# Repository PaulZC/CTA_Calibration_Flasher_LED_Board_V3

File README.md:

# CTA Calibration Flasher: LED Board V3

A nanosecond LED flasher board which provides digital control of both pulse width and LED current. Designed to aid
photomultiplier detector calibration and characterisation.

The design of this board is based extensively on that of the [Nanosecond LED Flasher Shield](https://github.com/PaulZC/Nanosecond_LED_Flasher_Shield).

The LED is driven by the [LMG1025 from Texas Instruments](http://www.ti.com/product/LMG1025-Q1).
Designed for automotive LIDAR applications, this gate driver has typical rise and fall times of 650ps
and 850ps and can produce 5V pulse widths as short as 1.25ns.

The pulse width is controlled by a [Maxim Integrated DS1023S-25+](https://www.maximintegrated.com/en/products/analog/clock-generation-distribution/DS1023.html)
programmable timing element which can produce digitally-adjustable pulse widths of 0 to ~64ns in 0.25ns increments.

The LED current is set by five surface mount resistors connected in series, four of which can be shorted
out by [Toshiba TLP3475 photorelays](https://toshiba.semicon-storage.com/ap-en/semiconductor/product/optoelectronics/photorelay-mosfet-output/detail.TLP3475.html)
allowing the LED current to be adjusted digitally in 16 increments.

The board is designed to be mounted on and controlled by the [CTA Calibration Flasher Controller Board V3](https://github.com/PaulZC/CTA_Calibration_Flasher_Controller_Board_V3).

The temperature can be measured via an [ADT7310 16-bit SPI temperature sensor](https://www.analog.com/en/products/adt7310.html).

The board is also equipped with a [DS28CM00 I<sup>2</sup>C silicon serial number](https://www.maximintegrated.com/en/products/ibutton-one-wire/memory-products/DS28CM00.html)
to allow the board to be uniquely identified during calibration.

To aid the mounting of a diffuser or fibre-coupling optics, a modified [ThorLabs S1LEDM SM1 threaded mount](https://www.thorlabs.de/thorproduct.cfm?partnumber=S1LEDM)
can be mounted onto the circuit board.

Please note that this board requires 5V power but that all I/O signals are 3.3V.

## Repository Contents

- **/Documentation** - Documentation for the hardware
- **/Hardware** - BOM, schematic, Eagle PCB design files and Gerber files
- **LICENSE.md** contains the licence information

## Documentation

- [Hardware overview](./Documentation/README.md): an overview of the hardware

Enjoy!

**_Paul_**

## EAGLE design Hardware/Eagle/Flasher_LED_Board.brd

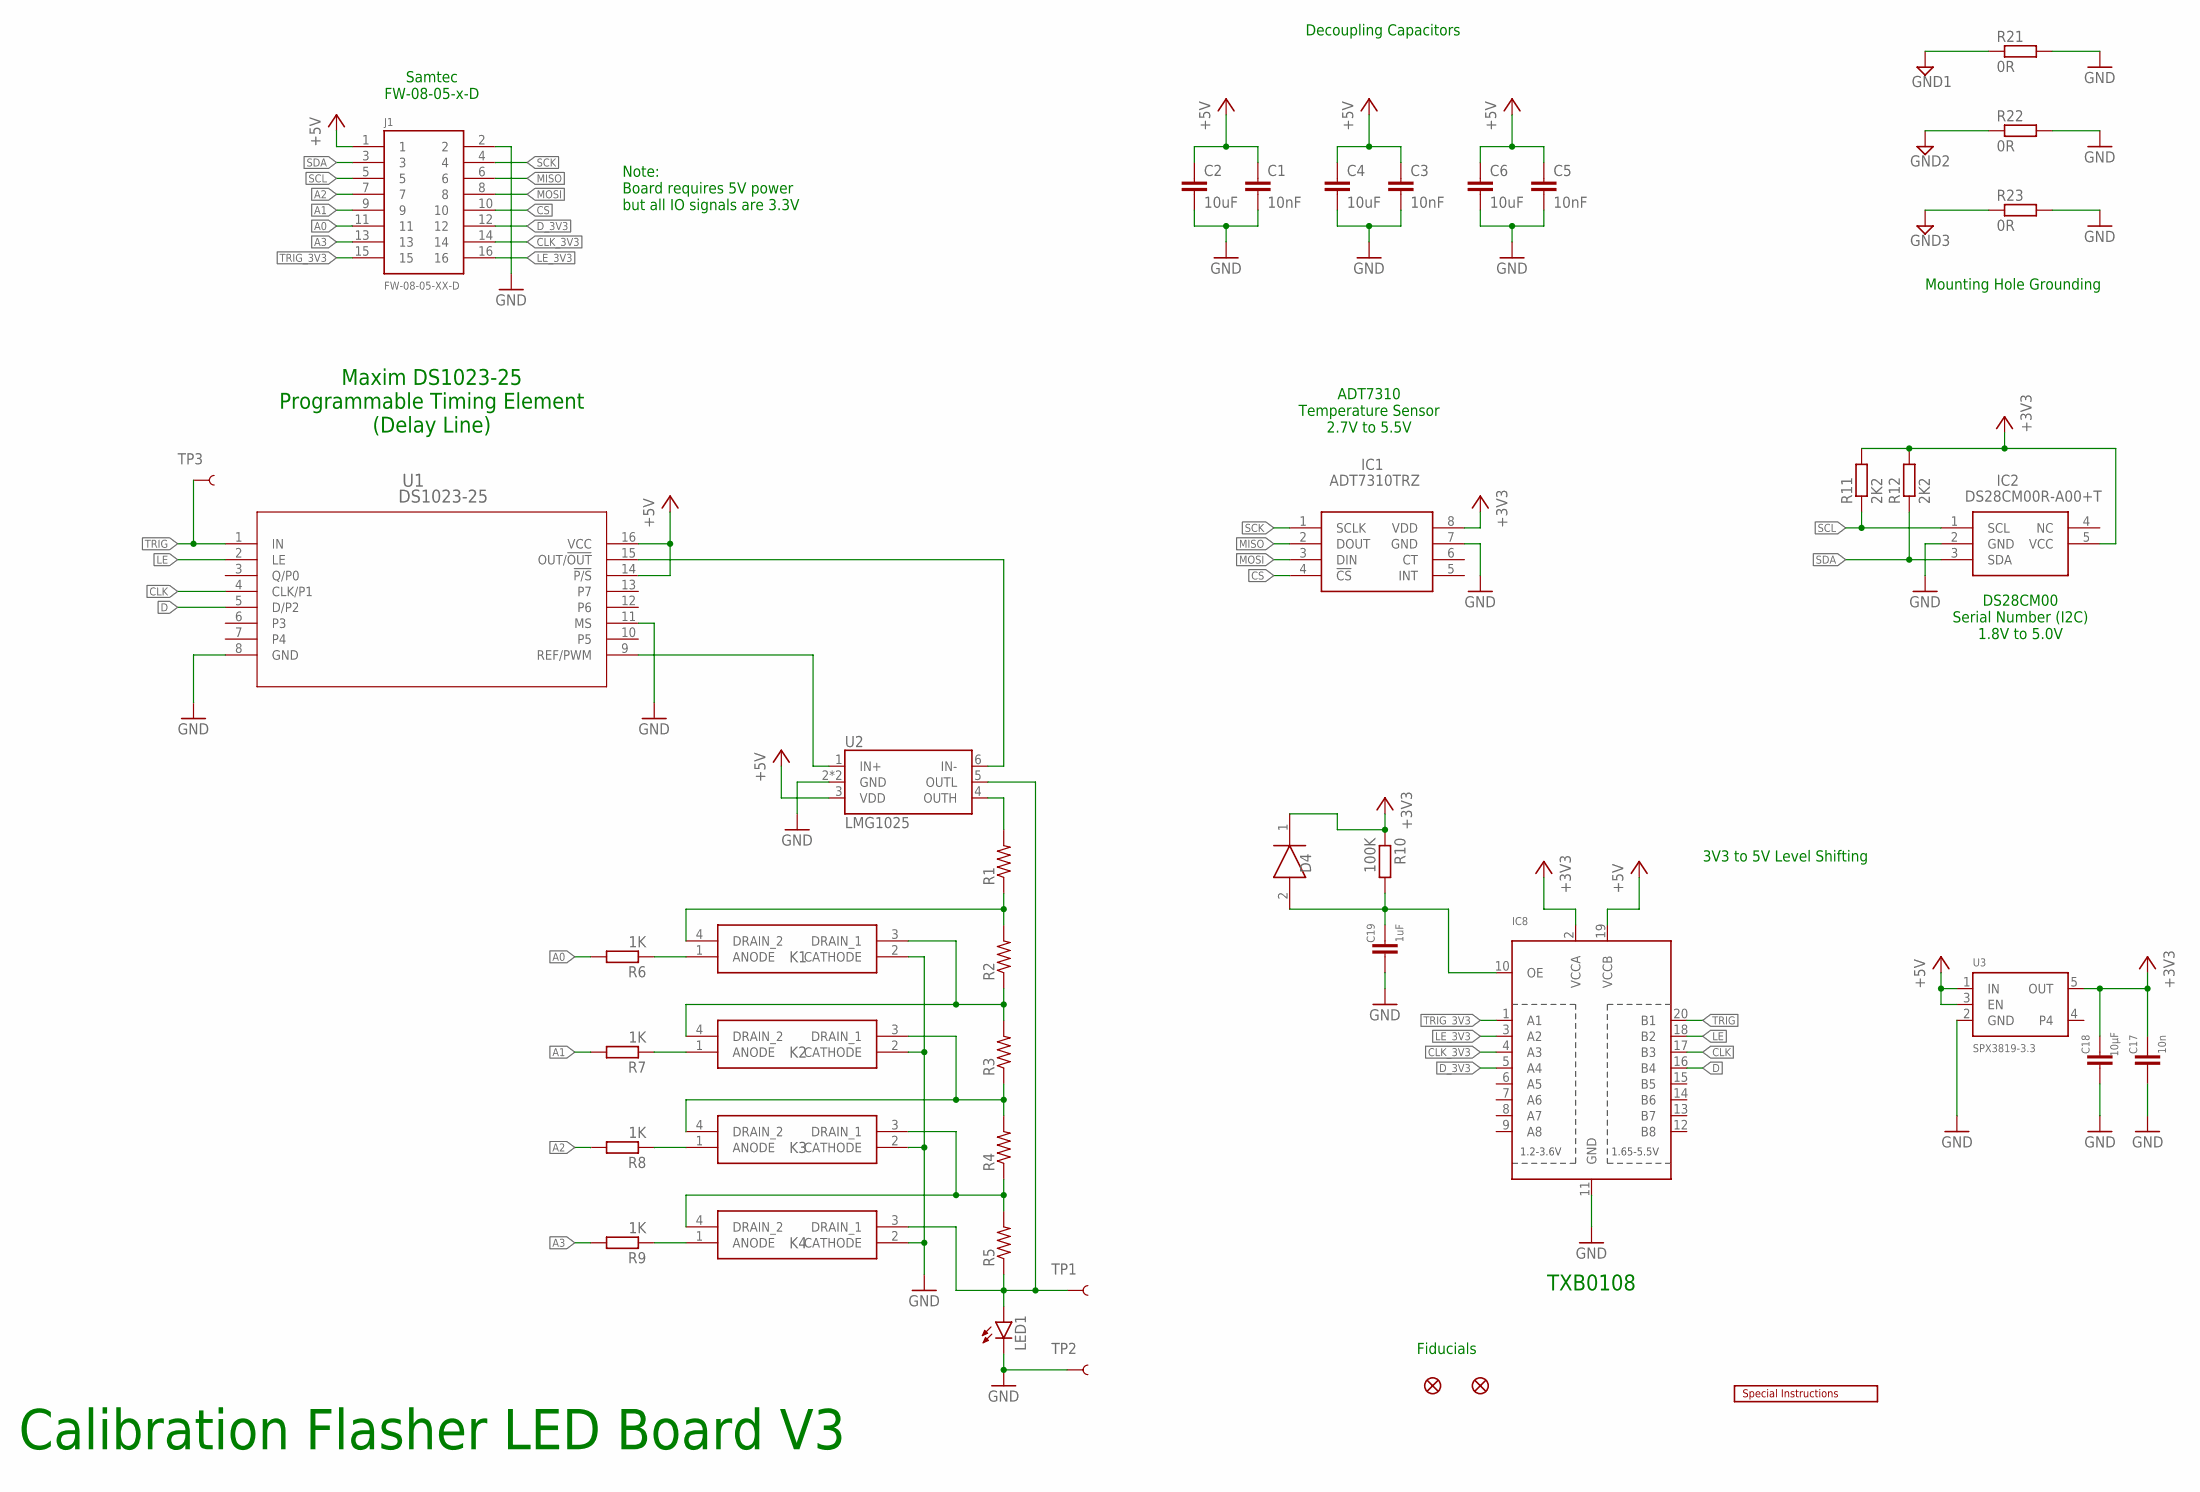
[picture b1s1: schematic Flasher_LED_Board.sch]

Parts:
C1, C3, C5: 10nF; C0805
C2, C4, C6: 10uF; C0805
C17: 10n; C0603
C18: 10µF; C0805
C19: 1uF; C0603
D4: CD0603-B00340; DIOM179X85N
FD1, FD2: FIDUCIAL1X2; FIDUCIAL-1X2
IC1: ADT7310TRZ; SOIC127P600X175-8N
IC2: DS28CM00R-A00+T; SOT95P280X145-5N
IC8: TXB0108PWR; TSSOP20
J1: FW-08-05-XX-D
K1, K2, K3, K4: TLP3475R(TP,F; TLP3475RTPF
LED1: LED3MM
LOGO6: SPECIAL_INSTRUCTIONS-ORDERING; ORDERING_INSTRUCTIONS
R1, R2, R3, R4, R5: RESISTOR0805-RES; 0805
R6, R7, R8, R9: 1K; R0603
R10: 100K; R0603
R11, R12: 2K2; R0603
R21, R22, R23: 0R; R0603
TP1, TP2, TP3: TEST-POINTPOGO_PTH; 1X01_NO_SILK
U1: DS1023-25; 21-0042B_16
U2: LMG1025
U3: SPX3819-3.3; SOT23-5

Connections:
+3V3: C17.1, C18.1, D4.1 (K), IC1.8 (VDD), IC2.5 (VCC), IC8.2 (VCCA), R10.1, R11.2, R12.2, U3.5 (OUT)
+5V: C1.1, C2.1, C3.1, C4.1, C5.1, C6.1, IC8.19 (VCCB), J1.1, U1.14 (!P/S), U1.16 (VCC), U2.3 (VDD), U3.1 (IN), U3.3 (EN)
A0: J1.11, R6.2
A1: J1.9, R7.2
A2: J1.7, R8.2
A3: J1.13, R9.2
CLK: IC8.17 (B3), U1.4 (CLK/P1)
CLK_3V3: IC8.4 (A3), J1.14
CS: IC1.4 (!CS), J1.10
D: IC8.16 (B4), U1.5 (D/P2)
D_3V3: IC8.5 (A4), J1.12
GND: C1.2, C2.2, C3.2, C4.2, C5.2, C6.2, C17.2, C18.2, C19.2, IC1.7 (GND), IC2.2 (GND), IC8.11 (GND), J1.2, K1.2 (CATHODE), K2.2 (CATHODE), K3.2 (CATHODE), K4.2 (CATHODE), LED1.K (C), R21.2, R22.2, R23.2, TP2.1, U1.8 (GND), U1.11 (MS), U2.2 (GND), U2.PAD (GND), U3.2 (GND)
GND1: R21.1
GND2: R22.1
GND3: R23.1
LE: IC8.18 (B2), U1.2 (LE)
LE_3V3: IC8.3 (A2), J1.16
MISO: IC1.2 (DOUT), J1.6
MOSI: IC1.3 (DIN), J1.8
unnamed: C19.1, D4.2 (A), IC8.10 (OE), R10.2
unnamed: U1.15 (OUT/!OUT), U2.6 (IN-)
unnamed: U1.9 (REF/PWM), U2.1 (IN+)
unnamed: R1.2, U2.4 (OUTH)
unnamed: K1.4 (DRAIN_2), R1.1, R2.2
unnamed: K1.3 (DRAIN_1), K2.4 (DRAIN_2), R2.1, R3.2
unnamed: K2.3 (DRAIN_1), K3.4 (DRAIN_2), R3.1, R4.2
unnamed: K3.3 (DRAIN_1), K4.4 (DRAIN_2), R4.1, R5.2
unnamed: K4.3 (DRAIN_1), LED1.A, R5.1, TP1.1, U2.5 (OUTL)
unnamed: K1.1 (ANODE), R6.1
unnamed: K2.1 (ANODE), R7.1
unnamed: K3.1 (ANODE), R8.1
unnamed: K4.1 (ANODE), R9.1
SCK: IC1.1 (SCLK), J1.4
SCL: IC2.1 (SCL), J1.5, R11.1
SDA: IC2.3 (SDA), J1.3, R12.1
TRIG: IC8.20 (B1), TP3.1, U1.1 (IN)
TRIG_3V3: IC8.1 (A1), J1.15

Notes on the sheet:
Calibration Flasher LED Board V3
Samtec FW-08-05-x-D
Fiducials
Mounting Hole Grounding
Decoupling Capacitors
Maxim DS1023-25 Programmable Timing Element (Delay Line)
ADT7310 Temperature Sensor 2.7V to 5.5V
DS28CM00 Serial Number (I2C) 1.8V to 5.0V
TXB0108
3V3 to 5V Level Shifting
Note: Board requires 5V power but all IO signals are 3.3V

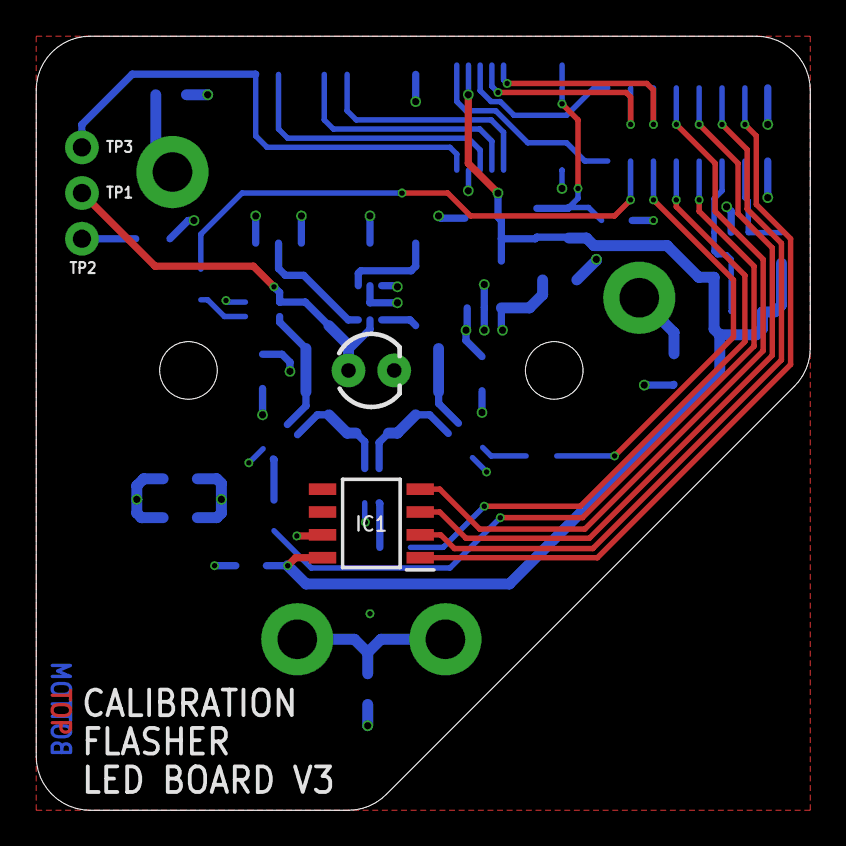
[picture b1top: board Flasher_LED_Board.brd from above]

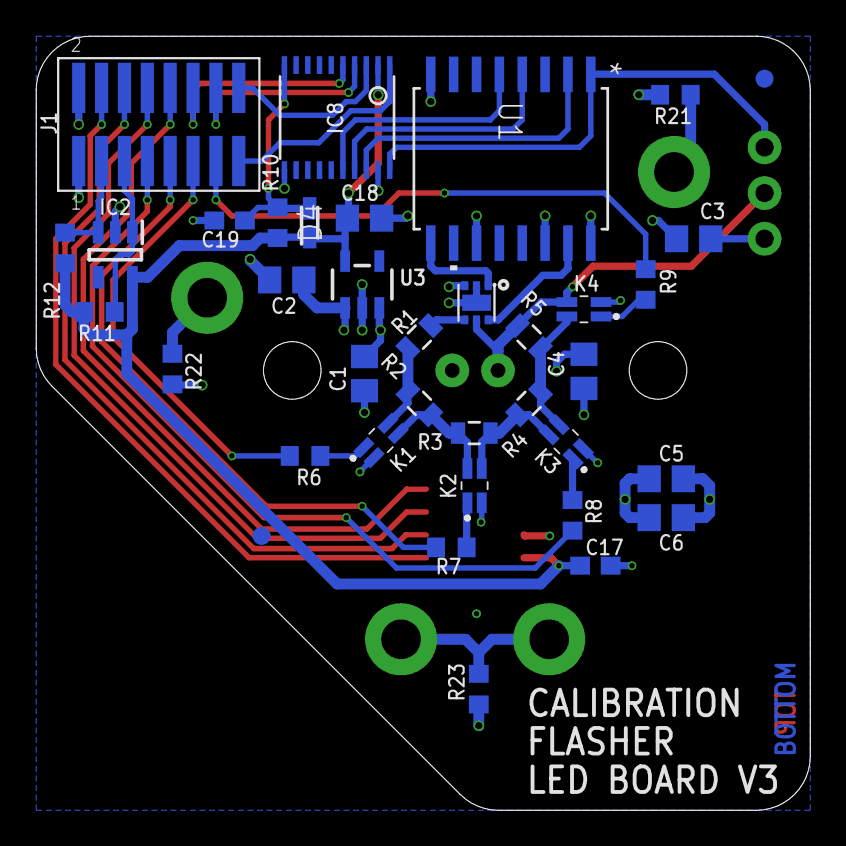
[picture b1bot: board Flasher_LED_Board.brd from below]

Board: 4 copper layers, 43.0 x 43.0 mm, 43 parts (37 on the bottom side), 34 nets.

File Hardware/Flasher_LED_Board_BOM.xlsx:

Part | X | X (Mirrored) | Y | Angle | Angle (Mirrored) | Package | Value | Manufacturer | Manufacturer Part No | Farnell Part No | Mouser Part No | Description
Dimensions | 43 |  | 43
Fiducials - for solder paste mask alignment:
FD1 | 2.54 | 40.46 | 40.64 | 0 |  |  |  |  |  |  |  | Fiducial 1mm
FD2 | 30.48 | 12.52 | 15.24 | 0 |  |  |  |  |  |  |  | Fiducial 1mm
Surface Mount Components (Top):
IC1 | 18.62 |  | 16.94 | 180 |  | 8-Lead SOIC_N (R-8) | ADT7310TRZ | Analog Devices | ADT7310TRZ | 2067805 | 584-ADT7310TRZ-R7 | Temperature Sensor IC, Digital, ± 0.5°C, -55 °C, +150 °C
Surface Mount Components (Bottom):
C1 | 24.77 | 18.23 | 24.26 | 270 |  | 0805 | 10nF | Walsin | 0805B103K500CT | 2496939 |  | MultiLayer Ceramic Capacitor; 10nF; 50V; 0805; X7R
C2 | 29.08 | 13.92 | 29.46 | 180 |  | 0805 | 10uF | Walsin | 0805F106Z100CT | 2496998 |  | MultiLayer Ceramic Capacitor; 10uF; 10V; 0805
C3 | 6.48 | 36.52 | 31.75 | 0 |  | 0805 | 10nF | Walsin | 0805B103K500CT | 2496939 |  | MultiLayer Ceramic Capacitor; 10nF; 50V; 0805; X7R
C4 | 12.57 | 30.43 | 24.38 | 90 |  | 0805 | 10uF | Walsin | 0805F106Z100CT | 2496998 |  | MultiLayer Ceramic Capacitor; 10uF; 10V; 0805
C5 | 8 | 35 | 18.41 | 0 |  | 0805 | 10nF | Walsin | 0805B103K500CT | 2496939 |  | MultiLayer Ceramic Capacitor; 10nF; 50V; 0805; X7R
C6 | 8 | 35 | 16.26 | 0 |  | 0805 | 10uF | Walsin | 0805F106Z100CT | 2496998 |  | MultiLayer Ceramic Capacitor; 10uF; 10V; 0805
C17 | 11.94 | 31.06 | 13.59 | 0 |  | 0603 | 10nF | Walsin | 0201B103K100CT | 2496756 |  | MultiLayer Ceramic Capacitor; 10nF; 10V; 0603; X7R
C18 | 24.77 | 18.23 | 32.89 | 0 |  | 0805 | 10uF | Walsin | 0805F106Z100CT | 2496998 |  | MultiLayer Ceramic Capacitor; 10uF; 10V; 0805
C19 | 32.26 | 10.74 | 32.77 | 180 |  | 0603 | 1uF | Walsin | 0603X105K100CT | 2496916 |  | MultiLayer Ceramic Capacitor; 1uF; 10V; 0603; X5R
D4 | 27.81 | 15.19 | 32.64 | 90 |  | 0603 | CD0603-B00340 | Bourns | CD0603-B00340 | 1456534 |  | Small Signal Schottky Diode, 40 V, 370 mV, 500 mA
IC2 | 38.61 | 4.39 | 30.86 | 270 |  | SOT23-5 | DS28CM00R-A00+T | Maxim | DS28CM00R-A00+T | 2514574 | 700-DS28CM00R-A00T | Maxim (Dallas Semi) I2C/SMBus Silicon Serial Number
IC8 | 26.29 | 16.71 | 38.48 | 180 |  | TSSOP20 | TXB0108PWR | Texas Inst. | TXB0108PWR | 1494945 |  | Voltage Level Translator; 8 Input; TSSOP-20
J1 | 36.2 | 6.8 | 38.1 | 0 |  |  |  | Samtec
K1 | 23.85 | 19.15 | 20.55 | 315 |  |  |  | Toshiba | TLP3475RTPF |  | 757-TLP3475TPF | Toshiba TLP3475 Photorelay (not TLP3475R)
K2 | 18.65 | 24.35 | 18.03 | 0 |  |  |  | Toshiba | TLP3475RTPF |  | 757-TLP3475TPF | Toshiba TLP3475 Photorelay (not TLP3475R)
K3 | 13.56 | 29.44 | 20.48 | 45 |  |  |  | Toshiba | TLP3475RTPF |  | 757-TLP3475TPF | Toshiba TLP3475 Photorelay (not TLP3475R)
K4 | 12.57 | 30.43 | 27.83 | 90 |  |  |  | Toshiba | TLP3475RTPF |  | 757-TLP3475TPF | Toshiba TLP3475 Photorelay (not TLP3475R)
R1 | 21.72 | 21.28 | 26.29 | 45 |  | 0805 |  |  |  |  |  | Select on test: suggested value 10R
R2 | 21.72 | 21.28 | 22.61 | 135 |  | 0805 |  |  |  |  |  | Select on test: suggested value 18R
R3 | 18.67 | 24.33 | 20.96 | 180 |  | 0805 |  |  |  |  |  | Select on test: suggested value 22R
R4 | 15.62 | 27.38 | 22.61 | 225 |  | 0805 |  |  |  |  |  | Select on test: suggested value 27R
R5 | 15.62 | 27.38 | 26.29 | 315 |  | 0805 |  |  |  |  |  | Select on test: suggested value 33R
R6 | 28.07 | 14.93 | 19.69 | 180 |  | 0603 | 1K | Multicomp | MCWR06X1001FTL | 2447272 |  | Chip Resistor; Thick Film; 1k; 50V; 0603; 100mW
R7 | 19.94 | 23.06 | 14.61 | 180 |  | 0603 | 1K | Multicomp | MCWR06X1001FTL | 2447272 |  | Chip Resistor; Thick Film; 1k; 50V; 0603; 100mW
R8 | 13.21 | 29.79 | 16.38 | 270 |  | 0603 | 1K | Multicomp | MCWR06X1001FTL | 2447272 |  | Chip Resistor; Thick Film; 1k; 50V; 0603; 100mW
R9 | 9.14 | 33.86 | 29.21 | 90 |  | 0603 | 1K | Multicomp | MCWR06X1001FTL | 2447272 |  | Chip Resistor; Thick Film; 1k; 50V; 0603; 100mW
R10 | 29.59 | 13.41 | 32.64 | 90 |  | 0603 | 100K | Multicomp | MCWR06X1002FTL | 2447230 |  | Chip Resistor; Thick Film; 10k; 50V; 0603; 100mW
R11 | 39.5 | 3.5 | 27.69 | 180 |  | 0603 | 2K2 | Multicomp | MCWR06X2201FTL | 2447320 |  | Chip Resistor; Thick Film; 2.2k; 50V; 0603; 100mW
R12 | 41.4 | 1.6 | 31.24 | 270 |  | 0603 | 2K2 | Multicomp | MCWR06X2201FTL | 2447320 |  | Chip Resistor; Thick Film; 2.2k; 50V; 0603; 100mW
R21 | 7.49 | 35.51 | 39.75 | 180 |  | 0603 | 0R | Multicomp | MCMR06X000PTL | 2073345 |  | SMD Chip Resistor, 0 ohm, 75 V, 0603, 100 mW
R22 | 35.43 | 7.57 | 24.51 | 270 |  | 0603 | 0R | Multicomp | MCMR06X000PTL | 2073345 |  | SMD Chip Resistor, 0 ohm, 75 V, 0603, 100 mW
R23 | 18.41 | 24.59 | 6.73 | 270 |  | 0603 | 0R | Multicomp | MCMR06X000PTL | 2073345 |  | SMD Chip Resistor, 0 ohm, 75 V, 0603, 100 mW
U1 | 16.64 | 26.36 | 36.2 | 270 |  | WSOIC-16 | DS1023-25 | Maxim | DS1023S-25+ | 2516605 | 700-DS1023S-25 | Delay Line; 256 taps; 250ps delay/tap; WSOIC-16
U2 | 18.54 | 24.46 | 28.19 | 180 |  | LMG1025 | LMG1025 |  |  |  |  | TI LMG1025: https://www.ti.com/product/LMG1025-Q1
U3 | 24.89 | 18.11 | 29.21 | 0 |  | SOT23-5 | SPX3819-3.3 | Exar | SPX3819M5-L-3-3/TR |  | 701-SPX3819M5-L-33TR | LDO Voltage Regulator; 500mA; SOT-23-5
Non-surface mount components:
LED |  |  |  |  |  |  |  | Bivar | UV3TZ-400-15 |  |  | Ultraviolet LED, 3mm, 10mW, 400nm, 15 deg, 3.3V, 20mA Max, RS Part: 713-5021P

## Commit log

2020-07-24 Updated the schematic
2020-08-29 Added the BOM

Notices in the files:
parts and their libraries:
SparkFun-Aesthetics: Licensing: Creative Commons ShareAlike 4.0 International - https://creativecommons.org/licenses/by-sa/4.0
microbuilder: This work is placed in the public domain, and may be freely used for commercial and non-commercial work with the following conditions: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
